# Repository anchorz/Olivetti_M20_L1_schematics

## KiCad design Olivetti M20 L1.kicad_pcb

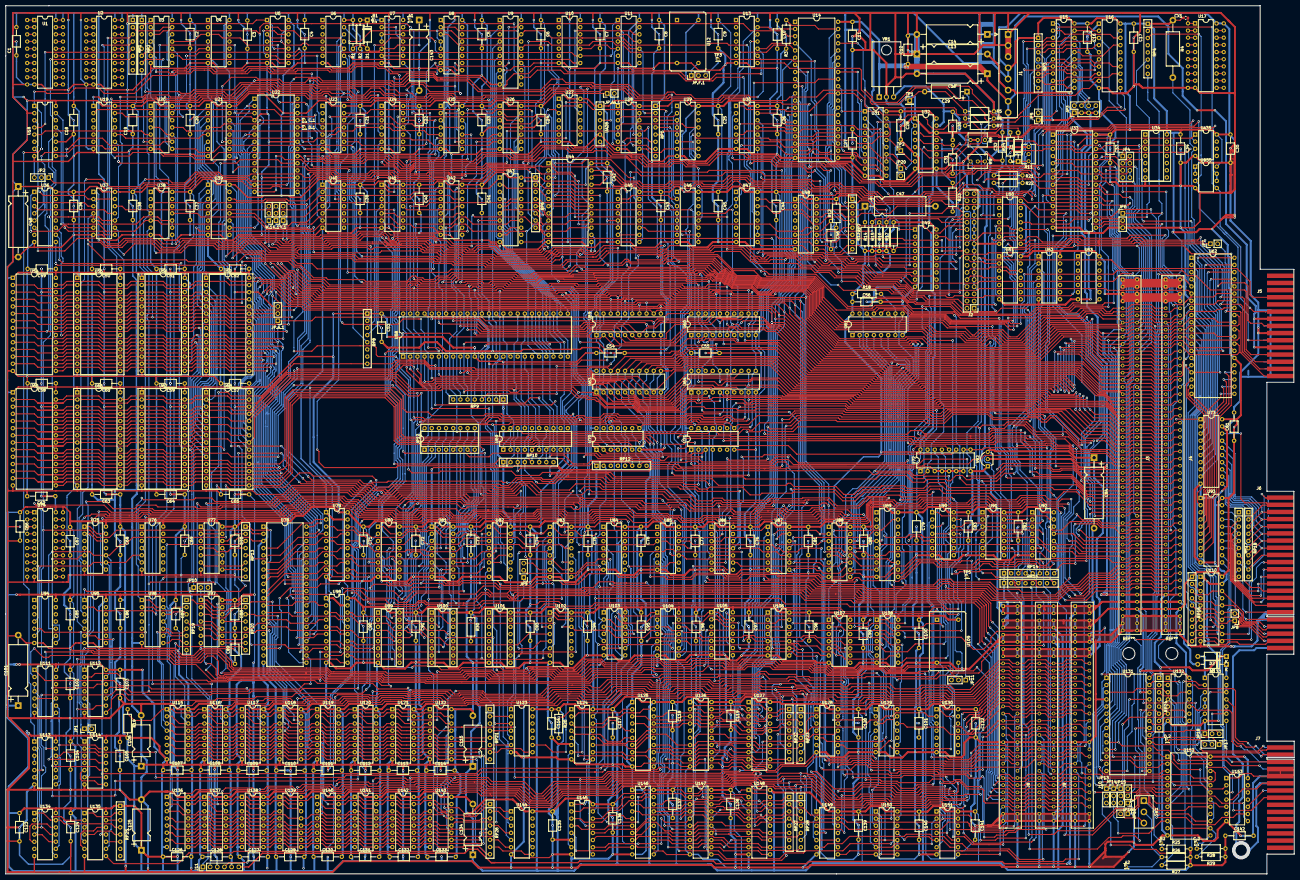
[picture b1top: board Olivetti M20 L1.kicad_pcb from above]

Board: 4 copper layers, 457.1 x 308.0 mm, 410 parts (0 on the bottom side), 747 nets.

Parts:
.A1, .A2, .B1, .B2: TestPoint; PinHeader_1x01_P1.00mm_Vertical
C1, C2, C3, C4, C5, C6, C7, C8, C9, C10, C11, C12, C16, C17, C18, C19, C20, C21, C22, C23, C24, C25, C26, C27, C28, C30, C33, C36, C37, C38, C39, C40, C41, C42, C43, C44, C45, C49, C50, C51, C52, C53, C54, C55, C56, C57, C58, C59, C60, C61, C62, C63, C64, C65, C66, C67, C68, C69, C70, C71, C72, C73, C74, C75, C76, C77, C78, C79, C80, C81, C82, C83, C85, C86, C87, C88, C89, C90, C91, C93, C94, C95, C96, C97, C98, C99, C100, C102, C103, C104, C105, C107, C108, C109, C110, C111, C112, C113, C114, C116, C117, C118, C119, C120, C121, C122, C123, C124, C126, C127, C128, C129, C130, C131, C132, C133, C135, C136, C137, C138, C139, C140, C141, C142: 100n; C_Axial_L3.8mm_D2.6mm_P10.00mm_Horizontal
C13, C14, C15, C48, C84: 47µ; CP_Axial_L18.0mm_D6.5mm_P25.00mm_Horizontal
C29: 0.68; CP_Axial_L10.0mm_D4.5mm_P15.00mm_Horizontal
C31: 100p; C_Axial_L3.8mm_D2.6mm_P10.00mm_Horizontal
C32, C46: C; C_Axial_L3.8mm_D2.6mm_P10.00mm_Horizontal
C34, C35: 1µ; C_Axial_L3.8mm_D2.6mm_P10.00mm_Horizontal
C47: 33µ; CP_Axial_L18.0mm_D6.5mm_P25.00mm_Horizontal
C101, C143: 22µ; CP_Axial_L18.0mm_D6.5mm_P25.00mm_Horizontal
C106, C115, C125, C134: 10µ; CP_Axial_L11.0mm_D6.0mm_P18.00mm_Horizontal
C.1, C.2: TestPoint; PinHeader_1x01_P1.00mm_Vertical
CX1: 1µ; C_0603_1608Metric
D1, D2, D3: 4148; D_A-405_P10.16mm_Horizontal
D.1, D.2: TestPoint; PinHeader_1x01_P1.00mm_Vertical
J1: 3.96mm; TE_826576-8_1x08_P3.96mm_Vertical
J2: Floppy Disk; PinHeader_2x17_P2.54mm_Vertical
J3, J4: EdgeCard100; Edge100
J5: VIDEO; Edge30_video
J6: Parallel; Edge44_pcb
J7: RS232; Edge30_pcb
J8, J9, J10: EdgeCard62; Edge62
J11: KBD; PinHeader_1x06_P2.54mm_Vertical
JP1: #DD; PinHeader_1x02_P2.54mm_Vertical
JP2: B; PinHeader_1x03_P2.54mm_Vertical
JP3: #X; PinHeader_2x04_P2.54mm_Vertical
JP4: Patch; PinHeader_2x04_P2.54mm_Vertical
JP5: #ZA; PinHeader_2x01_P2.54mm_Vertical
JP6: #E; PinHeader_1x03_P2.54mm_Vertical
JP7: #HH; PinHeader_1x02_P2.54mm_Vertical
JP8: #D; PinHeader_1x02_P2.54mm_Vertical
JP9: #JJ; PinHeader_1x03_P2.54mm_Vertical
JP10: #M; PinHeader_1x03_P2.54mm_Vertical
JP11: #G; PinHeader_1x03_P2.54mm_Vertical
JP12: Conn_02x08_Counter_Clockwise; DIP-16_W7.62mm_Socket
JP13: #C; PinHeader_1x03_P2.54mm_Vertical
JP14: #P; PinHeader_1x03_P2.54mm_Vertical
JP15: #N; PinHeader_1x03_P2.54mm_Vertical
JP16: #T; PinHeader_1x03_P2.54mm_Vertical
JP17: #R; PinHeader_1x03_P2.54mm_Vertical
JP18: #S; PinHeader_1x03_P2.54mm_Vertical
JP19: #FF; PinHeader_1x02_P2.54mm_Vertical
JP20: #CC; PinHeader_1x02_P2.54mm_Vertical
JP.A.1, JP.F.1: M20-Jumper.1; PinHeader_1x03_P2.54mm_Vertical
JP.AA.1: Conn_01x02_Male; PinHeader_1x02_P2.54mm_Vertical
K.1: M20-Jumper.2; PinHeader_1x03_P2.54mm_Vertical
R1: 22k; R_Axial_DIN0207_L6.3mm_D2.5mm_P10.16mm_Horizontal
R2: 47R; R_Axial_DIN0207_L6.3mm_D2.5mm_P10.16mm_Horizontal
R3: 10k; R_Axial_DIN0207_L6.3mm_D2.5mm_P10.16mm_Horizontal
R4: 30Ω; R_Axial_DIN0414_L11.9mm_D4.5mm_P20.32mm_Horizontal
R5, R6: 47.5k; R_Axial_DIN0207_L6.3mm_D2.5mm_P10.16mm_Horizontal
R7: 68; R_Axial_DIN0207_L6.3mm_D2.5mm_P10.16mm_Horizontal
R8: 100k; Potentiometer_Vishay_T73XW_Horizontal
R9: 50k; Potentiometer_Vishay_T73XW_Horizontal
R11: 10k; Potentiometer_Vishay_T73XW_Horizontal
R12, R14, R15, R16, R17, R21, R22: R; R_Axial_DIN0207_L6.3mm_D2.5mm_P10.16mm_Horizontal
R13: 47k; R_Axial_DIN0207_L6.3mm_D2.5mm_P10.16mm_Horizontal
R18, R20, R25, R26, R27, R28, R29: 1k; R_Axial_DIN0207_L6.3mm_D2.5mm_P10.16mm_Horizontal
R19, R24: 150R; R_Axial_DIN0207_L6.3mm_D2.5mm_P10.16mm_Horizontal
R23: 15k; R_Axial_DIN0207_L6.3mm_D2.5mm_P10.16mm_Horizontal
R30: 4.7k; R_Axial_DIN0207_L6.3mm_D2.5mm_P10.16mm_Horizontal
RP1, RP2, RP3, RP4, RP5, RP6, RP8, RP12, RP14, RP15, RP25: 1k; R_Array_SIP8
RP7, RP9, RP10: 10k; R_Array_SIP8
RP13, RP19, RP20: 33R; R_Array_SIP8
RP16, RP17, RP18: 1k; R_Array_SIP10
RP21, RP26: 33Ω; R_Array_SIP8
RP22, RP23, RP27, RP28: 120R; R_Array_SIP8
RP24: 27k; R_Array_SIP8
SW1: Reset-Button; TE_826576-3_1x03_P3.96mm_Vertical
TP1, TP2: TestPoint; PinHeader_1x01_P2.54mm_Vertical
TP3: TestPoint; PinHeader_1x01_P1.00mm_Vertical
TP5: EXT_PCLK; PinHeader_1x01_P1.00mm_Vertical
U1, U2, U17, U74: Spare20
U3, U25, U70, U87, U94, U149, U150: 'LS00; DIP-14_W7.62mm
U4, U30, U51: '16; DIP-14_W7.62mm
U5, U6, U52, U92: 'LS74; DIP-14_W7.62mm
U7: 'LS132; DIP-14_W7.62mm
U8, U42: 'LS138; DIP-16_W7.62mm
U9, U69, U79, U89, U98, U110, U127, U148: 'LS244; DIP-20_W7.62mm
U10, U13: 'LS32; DIP-14_W7.62mm
U11, U90, U134, U135: 'S74; DIP-14_W7.62mm
U12: 16MHz; Oscillator_DIP-14
U14: FD1797; DIP-40_W15.24mm
U15, U43, U125, U126, U146, U147: 'LS373; DIP-20_W7.62mm
U16: 'LS374; DIP-20_W7.62mm
U18: 'LS112; DIP-16_W7.62mm
U19, U77, U85, U91, U96, U108, U112, U123, U129, U144: 'S04; DIP-14_W7.62mm
U20, U50: 'S05; DIP-14_W7.62mm
U21, U39: 74LS138; DIP-16_W7.62mm
U22, U131: 8251; DIP-28_W15.24mm
U23, U103, U111, U130: 'S08; DIP-14_W7.62mm
U24, U95: 'LS02; DIP-14_W7.62mm
U26: 'LS260; DIP-14_W7.62mm
U27, U53: 'LS14; DIP-14_W7.62mm
U28, U97, U113, U114: 'S00; DIP-14_W7.62mm
U29, U45, U72: 74LS163; DIP-16_W7.62mm
U31: WD1691; DIP-20_W7.62mm
U32: 'LS629; DIP-16_W7.62mm
U33: 8259; DIP-28_W15.24mm
U34: SPARE; DIP-14_W7.62mm_Socket
U36: 'S138; DIP-16_W7.62mm
U37: 'LS08; DIP-14_W7.62mm
U38, U40, U86, U104: 'LS10; DIP-14_W7.62mm
U41: 'LS30; DIP-14_W7.62mm
U44: N82S181; DIP-24_W15.24mm
U46: 'LS163; DIP-16_W7.62mm
U47: 'LS123; DIP-16_W7.62mm
U48: 'LS221; DIP-16_W7.62mm
U49: WD2143M-03; DIP-18_W7.62mm
U54, U65: 27128; DIP-28_W15.24mm
U55, U56, U57, U66, U67, U68: 27128; DIP-28_W15.24mm_Socket
U58: Z8001; DIP-48_W15.24mm
U59, U63: 'S245; DIP-20_W7.62mm
U60, U64: 'S373; DIP-20_W7.62mm
U61: 'S163; DIP-16_W7.62mm
U62: 8255; DIP-40_W15.24mm
U71, U128: 'LS04; DIP-14_W7.62mm
U73, U93: 'LS245; DIP-20_W7.62mm
U75, U105, U107: 'LS20; DIP-14_W7.62mm
U76, U106: 'S32; DIP-14_W7.62mm
U78: MC6845; DIP-40_W15.24mm
U80, U81, U82, U83, U102: 'S253; DIP-16_W7.62mm
U84: PE-21389; DIP-14_W7.62mm
U88: 'LS670; DIP-16_W7.62mm
U99, U100, U101: SPARE; DIP-16_W7.62mm_Socket
U109: 12MHz; Oscillator_DIP-14
U115, U116, U117, U118, U119, U120, U121, U122, U136, U137, U138, U139, U140, U141, U142, U143: 41256; DIP-16_W7.62mm
U124, U145: 'LS166; DIP-16_W7.62mm
U132, U153: 75189; DIP-14_W7.62mm
U133: 75188; DIP-14_W7.62mm
U151: 'S20; DIP-14_W7.62mm
U152: 8253; DIP-24_W15.24mm
UA28: HH3006A; R_Array_SIP6
UA35: 75451; DIP-8_W7.62mm
UB35: 75451; DIP-8_W7.62mm
V.1: M20-Jumper.1; PinHeader_1x03_P2.54mm_Vertical
VR1: UA7805UC; TO-220-3_Horizontal_TabDown
VR2: 79L05; TO-92_Inline_Wide
W.1: M20-Jumper.2; PinHeader_1x03_P2.54mm_Vertical
Z1: 8.2V; D_A-405_P10.16mm_Horizontal

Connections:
32^128: JP3.6, RP3.3, U15.17, U44.1
+5P: C1.1, C2.1, C3.1, C4.1, C5.1, C6.1, C7.1, C8.1, C9.1, C10.1, C13.1, C16.1, C17.1, C18.1, C19.1, C20.1, C21.1, C22.1, C23.1, C24.1, C25.1, C26.1, C27.1, C28.1, C33.1, C34.1, C35.1, C36.1, C37.1, C38.1, C39.1, C40.1, C41.1, C42.1, C43.1, C44.1, C45.1, C48.1, C49.1, C50.1, C51.1, C52.1, C53.1, C54.1, C55.1, C56.1, C57.1, C58.1, C59.1, C60.1, C61.1, C62.1, C63.1, C64.1, C65.1, C66.1, C67.1, C68.1, C69.1, C70.1, C71.1, C72.1, C73.1, C74.1, C75.1, C76.1, C77.1, C78.1, C79.1, C80.1, C81.1, C82.1, C83.1, C85.1, C86.1, C87.1, C88.1, C89.1, C90.1, C91.1, C93.1, C94.1, C95.1, C96.1, C97.1, C98.1, C99.1, C100.1, C101.1, C102.1, C103.1, C104.1, C105.1, C106.1, C107.1, C108.1, C109.1, C110.1, C111.1, C112.1, C113.1, C114.1, C115.1, C116.1, C117.1, C118.1, C119.1, C120.1, C121.1, C122.1, C123.1, C124.1, C125.1, C126.1, C127.1, C128.1, C129.1, C130.1, C131.1, C132.1, C133.1, C134.1, C135.1, C136.1, C137.1, C138.1, C139.1, C140.1, C141.1, C142.1, CX1.1, J1.4, J1.5, J3.5, J3.6, J3.7, J3.8, J3.93, J3.94, J4.5, J4.6, J4.7, J4.8, J4.93, J4.94, J8.5, J8.6, J8.7, J8.8, J9.5, J9.6, J9.7, J9.8, J10.5, J10.6, J10.7, J10.8, J11.3, JP.A.1.3, R1.1, R2.2, R3.2, R4.1, R12.2, R13.1, R14.1, R15.1, R16.1, R17.2, R18.1, R19.2, R20.1, R25.2, R26.2, R27.1, R28.1, R29.1, R30.1, RP1.1, RP2.1, RP3.1, RP4.1, RP5.1, RP6.1, RP7.1, RP8.1, RP9.1, RP10.1, RP12.1, RP14.1, RP15.1, RP16.1, RP17.1, RP18.1, RP25.1, U1.20, U1.40, U2.20, U2.40, U3.14, U4.14, U5.14, U6.14, U7.14, U8.16, U9.20, U10.14, U11.14, U12.14, U13.14, U14.21, U15.20, U16.20, U17.20, U17.40, U18.16, U19.14, U20.14, U21.16, U22.26, U23.14, U24.14, U25.14, U26.14, U27.14, U28.14, U29.16, U30.14, U31.20, U32.16, U33.28, U34.14, U36.16, U37.14, U38.14, U39.16, U40.14, U41.14, U42.16, U43.20, U44.24, U45.16, U46.16, U47.16, U48.16, U49.18, U50.14, U51.14, U52.14, U53.14, U54.1, U54.26, U54.28, U55.1, U55.26, U55.28, U56.1, U56.26, U56.28, U57.1, U57.26, U57.28, U58.11, U59.20, U60.20, U61.16, U62.26, U63.20, U64.20, U65.1, U65.26, U65.28, U66.1, U66.26, U66.28, U67.1, U67.26, U67.28, U68.1, U68.26, U68.28, U69.20, U70.14, U71.14, U72.16, U73.20, U74.20, U74.40, U75.14, U76.14, U77.14, U78.20, U79.20, U80.16, U81.16, U82.16, U83.16, U84.14, U85.14, U86.14, U87.14, U88.16, U89.20, U90.14, U91.14, U92.14, U93.20, U94.14, U95.14, U96.14, U97.14, U98.20, U99.16, U100.16, U101.16, U102.16, U103.14, U104.14, U105.14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
+5VA: C30.1, C32.1, R8.2, R8.3, R21.1, U32.15, VR1.3
+12V: C11.1, C12.1, C15.1, D3.2, J1.7, J1.8, J3.91, J3.92, J4.91, J4.92, J5.14, J5.22, J8.1, J8.2, J8.3, J8.4, J9.1, J9.2, J9.3, J9.4, J10.1, J10.2, J10.3, J10.4, J11.6, R24.2, U14.40, VR1.1
-5V: C84.1, J8.13, J8.14, J8.15, J8.16, J9.13, J9.14, J9.15, J9.16, J10.13, J10.14, J10.15, J10.16, VR2.3
-12V: C14.2, D2.1, J1.6, J3.89, J3.90, J4.89, J4.90, RP24.1, VR2.2
-PCLK: U52.3, U85.4, U92.12, U107.1
/AD Mux/PL024: U59.19, U63.19, U70.6
/CLK_IO/PM002: U11.8, U28.10
/CLK_IO/PM003: U28.8, U29.7, U29.10
/CLK_IO/PM004: JP.F.1.1, U12.8
/CLK_IO/PM005: U11.3, U11.11, U28.3, U29.2, U45.2, U46.2
/CLK_IO/PM006: JP.F.1.2, U28.1, U28.2
/CLK_IO/PM010: U28.11, U45.9
/CLK_IO/PM011: U28.12, U28.13, U45.15
/CLK_IO/PM012: U11.12, U27.12
/CLK_IO/PM013: U27.2, U27.13
/CLK_IO/PM016: U3.2, U3.4, U24.13
/CLK_IO/PM017: U19.11, U26.5, U39.6
/CLK_IO/PM018: U19.10, U21.5
/CLK_IO/PM019: JP.F.1.3, TP3.1
/CLK_IO/PZ128: JP.AA.1.2, U28.6
/CLK_IO/R1402: RP5.3, U29.1, U29.3, U29.4, U29.5, U29.6, U29.9
/CLK_IO/RP5A: RP5.2, U11.4, U11.10
/CLK_IO/RP5F: RP5.7, U11.13
/CPU/PK000: U7.3, U7.4, U7.12
/CPU/PK001: U7.2, U7.11
/CPU/PK002: U7.6, U7.9, U7.10, U50.9
/CPU/PK003: U7.8, U58.16
/CPU/PK004: U6.9, U58.14
/CPU/PK005: U6.12, U40.12
/CPU/PK006: U25.3, U40.1
/CPU/PK011: U43.3, U58.26
/CPU/PK012: U43.4, U58.25
/CPU/PK013: U43.7, U58.37
/CPU/PK014: U43.8, U58.24
/CPU/PK015: U43.13, U58.42
/CPU/PK016: U43.14, U58.46
/CPU/PK017: U43.17, U58.47
/CPU/PK022: U8.7, U20.13
/CPU/PK030: U19.13, U26.6
/CPU/PK031: U19.12, U40.2
/CPU/PK033: U33.19, U91.8
/CPU/PK034: U33.20, U91.10
/CPU/PK037: U33.25, U91.6
/CPU/PK038: U33.17, U50.11
/CPU/PK040: U5.6, U5.12, U23.4
/CPU/PK041: U3.9, U5.8
/CPU/PK042: U3.8, U3.12
/CPU/PZ116: U8.9, U23.9
/CPU/R0028: C143.1, D1.2, R1.2, U7.5
/CPU/R0033: .B1.1, .B2.1, R25.1, SW1.1, U7.1
/CPU/R0034: .A1.1, .A2.1, R26.1, SW1.2, U7.13
/CPU/R0035: D1.1, R2.1
/CPU/R0705: RP9.8, U58.7
/CPU/R0706: RP9.7, U58.8
/CPU/XA.4.4: RP2.6, U4.4, U4.5
/CPU/XR.2.2: RP2.2, U5.1, U5.10
/CRTC/PE000: U78.4, U79.2
/CRTC/PE001: U78.5, U79.4
/CRTC/PE002: U78.6, U79.17
/CRTC/PE003: U78.7, U79.6
/CRTC/PE004: U78.8, U79.15
/CRTC/PE005: U78.9, U79.8
/CRTC/PE006: U78.10, U79.13
/CRTC/PE007: U78.11, U79.11
/CRTC/PE008: U78.12, U98.2
/CRTC/PE009: U78.13, U98.17
/CRTC/PE010: U78.14, U98.4
/CRTC/PE011: U78.15, U98.15
/CRTC/PE012: U78.38, U98.6
/CRTC/PE013: U78.37, U98.13
/CRTC/PE014: U78.36, U98.8
/CRTC/PE015: U78.35, U98.11
/CRTC/PZ054: R30.2, U102.15
/DRAM/PD000: JP10.2, U97.1, U97.4, U97.10, U97.13
/DRAM/PD003.1: RP13.5, U119.3, U120.3, U121.3, U122.3
/DRAM/PD003.2: RP13.8, U115.3, U116.3, U117.3, U118.3
/DRAM/PD004.1: RP19.3, U96.12
/DRAM/PD004.2: RP19.5, U96.10
/DRAM/PD005.1: RP19.4, U119.4, U120.4, U121.4, U122.4
/DRAM/PD005.2: RP19.6, U115.4, U116.4, U117.4, U118.4
/DRAM/PD007.1: RP20.5, U119.15, U120.15, U121.15, U122.15
/DRAM/PD007.2: RP20.8, U115.15, U116.15, U117.15, U118.15
/DRAM/PD009: RP21.1, U115.5, U116.5, U117.5, U118.5, U119.5, U120.5, U121.5, U122.5, U136.5, U137.5, U138.5, U139.5, U140.5, U141.5, U142.5, U143.5
/DRAM/PD011: RP21.8, U115.7, U116.7, U117.7, U118.7, U119.7, U120.7, U121.7, U122.7, U136.7, U137.7, U138.7, U139.7, U140.7, U141.7, U142.7, U143.7
/DRAM/PD013: RP21.3, U115.6, U116.6, U117.6, U118.6, U119.6, U120.6, U121.6, U122.6, U136.6, U137.6, U138.6, U139.6, U140.6, U141.6, U142.6, U143.6
/DRAM/PD015: RP21.5, U115.12, U116.12, U117.12, U118.12, U119.12, U120.12, U121.12, U122.12, U136.12, U137.12, U138.12, U139.12, U140.12, U141.12, U142.12, U143.12
/DRAM/PD016: RP26.2, U144.2
/DRAM/PD017: RP26.1, U115.11, U116.11, U117.11, U118.11, U119.11, U120.11, U121.11, U122.11, U136.11, U137.11, U138.11, U139.11, U140.11, U141.11, U142.11, U143.11
/DRAM/PD018: RP26.6, U144.6
/DRAM/PD019: RP26.5, U115.10, U116.10, U117.10, U118.10, U119.10, U120.10, U121.10, U122.10, U136.10, U137.10, U138.10, U139.10, U140.10, U141.10, U142.10, U143.10
/DRAM/PD020: RP26.4, U144.4
/DRAM/PD021: RP26.3, U115.13, U116.13, U117.13, U118.13, U119.13, U120.13, U121.13, U122.13, U136.13, U137.13, U138.13, U139.13, U140.13, U141.13, U142.13, U143.13
/DRAM/PD024: RP26.8, U115.9, U116.9, U117.9, U118.9, U119.9, U120.9, U121.9, U122.9, U136.9, U137.9, U138.9, U139.9, U140.9, U141.9, U142.9, U143.9
/DRAM/PD025: RP20.4, U97.11
/DRAM/PD026.1: RP20.3, U140.15, U141.15, U142.15, U143.15
/DRAM/PD026.2: RP20.1, U136.15, U137.15, U138.15, U139.15
/DRAM/PD027.1: RP19.2, U96.2
/DRAM/PD027.2: RP19.7, U96.8
/DRAM/PD028.1: RP19.1, U140.4, U141.4, U142.4, U143.4
/DRAM/PD028.2: RP19.8, U136.4, U137.4, U138.4, U139.4
/DRAM/PD029: U77.2, U77.3, U77.13
/DRAM/PD030.1: RP13.2, U77.12
/DRAM/PD030.2: RP13.4, U77.4
/DRAM/PD031.1: RP13.1, U140.3, U141.3, U142.3, U143.3
/DRAM/PD031.2: RP13.3, U136.3, U137.3, U138.3, U139.3
/DRAM/PD032: R19.1, U115.1, U116.1, U117.1, U118.1, U119.1, U120.1, U121.1, U122.1, U136.1, U137.1, U138.1, U139.1, U140.1, U141.1, U142.1, U143.1
/DRAM/ras.int: U96.1, U96.9, U96.11, U96.13, U129.2
/FDC+Latch/PA000: U15.3, U16.2, U51.3
/FDC+Latch/PA001: U15.4, U16.5, U51.13
/FDC+Latch/PA002: U15.7, U16.6, U51.1
/FDC+Latch/PA003: U14.37, U16.9, U31.15
/FDC+Latch/PA004: JP5.2, RP3.8, U15.8
/FDC+Latch/PA005: U14.26, U31.12
/FDC+Latch/PA006: U14.30, U30.1, U31.7
/FDC+Latch/PA007: JP20.2, U14.31, U31.1
/FDC+Latch/PA008: U14.17, U31.17
/FDC+Latch/PA009: U14.18, U31.18
/FDC+Latch/PA010: U14.33, U31.8
/FDC+Latch/PA011: JP20.1, U30.9, U31.6
/FDC+Latch/PA012: C29.2, R5.1, R6.1, TP1.1, U31.13, U31.14, U32.2
/FDC+Latch/PA015: R9.3, R22.1, R23.1, U32.3
/FDC+Latch/PA016: C31.2, U32.4
/FDC+Latch/PA017: C31.1, U32.5
/FDC+Latch/PA018: U14.27, U31.11, U48.12
/FDC+Latch/PA019: U13.8, U15.1
/FDC+Latch/PA022: U13.11, U16.11
/FDC+Latch/PA023: U14.23, U14.28
/FDC+Latch/PA024: U14.32, U47.13
/FDC+Latch/PA025: U14.25, U30.5
/FDC+Latch/PA026: U14.16, U30.11
/FDC+Latch/PA027: U14.15, U30.13
/FDC+Latch/PA031: RP7.7, U47.2, U47.3
/FDC+Latch/PA032: C47.2, U47.14
/FDC+Latch/PA046: TP2.1, U31.16, U32.7
/FDC+Latch/PA080: U31.19, U49.1
/FDC+Latch/PA081: U31.3, U49.3
/FDC+Latch/PA082: U31.2, U49.5
/FDC+Latch/PA083: U31.4, U49.7
/FDC+Latch/PA084: U16.19, U31.9
/FDC+Latch/PA085: R11.2, U49.17
/FDC+Latch/PA086: U31.5, U49.11
/FDC+Latch/PA087: R11.1, R24.1, Z1.1
/Latch/PC003: U124.2, U125.2
/Latch/PC004: U124.3, U125.5
/Latch/PC005: U124.4, U125.6
/Latch/PC006: U124.5, U125.9
/Latch/PC007: U124.10, U125.12
/Latch/PC008: U124.11, U125.15
/Latch/PC009: U124.12, U125.16
/Latch/PC010: U124.14, U125.19
/Latch/PC011: U145.2, U146.2
/Latch/PC012: U145.3, U146.5
/Latch/PC013: U145.4, U146.6
/Latch/PC014: U145.5, U146.9
/Latch/PC015: U145.10, U146.12
/Latch/PC016: U145.11, U146.15
/Latch/PC017: U145.12, U146.16
/Latch/PC018: U145.14, U146.19
/Latch/PC019: U105.6, U127.1, U127.19
/Latch/PC020: U124.13, U145.1
/Latch/PC023: U105.8, U148.1, U148.19
/Latch/PC024: RP23.2, U125.3, U126.3, U127.18
/Latch/PC025: RP23.4, U125.4, U126.4, U127.16
/Latch/PC026: RP22.6, U125.7, U126.7, U127.14
/Latch/PC027: RP22.8, U125.8, U126.8, U127.12
/Latch/PC028: RP23.8, U125.13, U126.13, U127.9
/Latch/PC029: RP23.6, U125.14, U126.14, U127.7
/Latch/PC030: RP22.3, U125.17, U126.17, U127.5
/Latch/PC031: RP22.1, U125.18, U126.18, U127.3
/Latch/PC032: RP28.2, U146.3, U147.3, U148.18
/Latch/PC033: RP28.4, U146.4, U147.4, U148.16
/Latch/PC034: RP27.6, U146.7, U147.7, U148.14
/Latch/PC035: RP27.8, U146.8, U147.8, U148.12
/Latch/PC036: RP28.8, U146.13, U147.13, U148.9
/Latch/PC037: RP28.6, U146.14, U147.14, U148.7
/Latch/PC038: RP27.3, U146.17, U147.17, U148.5
/Latch/PC039: RP27.1, U146.18, U147.18, U148.3
/Latch/SRAM: U86.3, U87.3
/PIO/PJ000: U62.4, U73.2
/PIO/PJ001: U62.3, U73.3
/PIO/PJ002: U62.2, U73.4
/PIO/PJ003: U62.1, U73.5
/PIO/PJ004: U62.40, U73.6
/PIO/PJ005: U62.39, U73.7
/PIO/PJ006: U62.38, U73.8
/PIO/PJ007: U62.37, U73.9
/PIO/PJ008: U62.18, U93.2
/PIO/PJ009: U62.19, U93.3
/PIO/PJ010: U62.20, U93.4
/PIO/PJ011: U62.21, U93.5
/PIO/PJ012: U62.22, U93.6
/PIO/PJ013: U62.23, U93.7
/PIO/PJ014: U62.24, U93.8
/PIO/PJ015: U62.25, U93.9
/PIO/PJ016: U62.15, U110.4
/PIO/PJ017: U62.16, U110.5
/PIO/PJ018: U62.13, U110.13
/PIO/PJ019: U62.12, U110.8
/PIO/PJ020: U62.11, U110.9
/PIO/PJ021: U62.10, U110.17
/PIO/PJ022: U92.3, U152.17
/PIO/R0302: RP16.6, U73.1
/PIO/R4907: RP14.5, U92.2, U92.4
/ROM/PG000: U38.6, U54.22, U55.22, U56.22, U57.22, U65.22, U66.22, U67.22, U68.22
/ROM/PG001: JP.A.1.2, U54.23, U55.23, U56.23, U57.23, U65.23, U66.23, U67.23, U68.23
/ROM/PG006: U36.15, U54.20, U65.20
/ROM/PG007: U36.11, U55.20, U66.20
/ROM/PG008: U36.10, U56.20, U67.20
/ROM/PG009: U36.9, U57.20, U68.20
/ROM/PG010: U36.1, U37.6
/ROM/PG011: U36.2, U37.3
/ROM/PG012: U36.3, U37.11
/ROM/PG013: U18.3, U18.7, U37.2, U37.5, U37.13, U38.9, U38.10
/ROM/PG014: U36.6, U38.8
/ROM/PG016: U18.5, U20.5
/ROM/PG017: U18.15, U37.8
/ROM/PG018: U19.8, U36.5
/ROM/R0007: RP1.4, U54.27, U55.27, U56.27, U57.27
/ROM/R2007: RP1.3, U65.27, U66.27, U67.27, U68.27
/ROM/R2907: RP1.5, U18.4
/ROM/R3907: RP1.6, U18.14
/ROM/XA.23.11: U20.11, U23.11
/ROM/XA.25.8: U23.13, U25.8
/ROM/XA.27.4: U20.3, U27.4
/Serial/PH004: U131.3, U132.3
/Serial/PH005: JP15.1, U132.6
/Serial/PH006: JP16.3, U132.8
/Serial/PH007: JP16.2, U131.17
/Serial/PH008: U131.22, U132.11
/Serial/PH009: U131.19, U133.4, U133.5
/Serial/PH010: JP18.3, U131.23
/Serial/PH011: JP17.1, U131.24
/Serial/PH012: JP18.2, U133.9, U133.10
/Serial/PH013: JP17.2, U133.12, U133.13
/Serial/PH020: JP15.3, U131.25
/Serial/PH022: JP13.2, U133.2
/Serial/PH038: RP24.8, U153.9
/Serial/PH039: RP24.6, U153.5
/Serial/PH040: RP24.7, U153.2
/State/PF011: U61.1, U90.9, U130.1
/State/PF012: U53.8, U87.12, U88.11
/State/PF013: U87.11, U89.19
/State/PF015: U52.5, U90.12
/State/PF016: U90.3, U108.8
/State/PF017: U90.5, UA35.1
/State/PF018: U72.14, U108.13
/State/PF019: U72.13, U107.4
/State/PF020: U72.12, U108.1
/State/PF021: U107.5, U108.2
/State/PF022: JP11.3, U109.8
/State/PF029: JP11.2, U87.9, U87.10, U108.3, U108.11
/State/PF031: JP6.2, U53.9
/State/PF081: U61.9, U90.8
/State/R1402: RP14.7, U72.1, U72.3, U72.4, U72.5, U72.6, U72.7, U72.9, U72.10
/State/RP14E: RP14.6, U52.4, U90.4, U90.10
/State/color_write: U88.12, U106.11
/Timings/A0=0: U150.1, U150.8
/Timings/Delay+50: U84.12, U103.10
/Timings/Delay+100: U84.4, U103.4
/Timings/Delay+150: U84.10, U103.13
/Timings/Delay+200: U84.6, U103.1
/Timings/Delay+250: U84.8, U114.2
/Timings/PB000: U41.1, U42.15
/Timings/PB001: U41.12, U42.14
/Timings/PB002: U41.11, U42.13
/Timings/PB003: U41.5, U42.12
/Timings/PB004: U42.11, U149.1
/Timings/PB005: U42.10, U128.9, U149.12
/Timings/PB006: U42.9, U128.5, U149.4
/Timings/PB007: U42.7, U128.11, U149.9
/Timings/PB008: U42.4, U95.6, U104.13, U135.9
/Timings/PB010: U25.4, U25.11, U40.5
/Timings/PB011: U24.4, U25.5, U40.4
/Timings/PB022: U75.2, U75.12, U95.4
/Timings/PB023: U75.4, U75.5, U94.8
/Timings/PB024: U75.10, U94.10, U112.10, U151.4, U151.10
/Timings/PB035: U129.8, U150.13
/Timings/PB036: U85.8, U85.11, U85.13, U112.1
/Timings/PB039: U150.11, U151.5, U151.9
/Timings/PB040: U94.9, U112.12
/Timings/PZ023: U86.9, U128.4
/Timings/R1102: RP8.4, U41.2, U41.3, U41.4
/Timings/R1102.A: RP25.2, U135.1
/Timings/R1102.B: RP25.3, U135.13
/Timings/R1102.C: RP25.4, U134.1, U134.13
/Timings/R1102.D: RP25.5, U135.4
/Timings/R1102.E: RP25.6, U135.10
/Timings/R1105: RP8.2, W.1.1
/Timings/X.103.3: U103.3, U104.2, U104.3, U104.9, U129.9
/Timings/X.103.6: U75.1, U75.13, U85.5, U103.6, U104.1, U104.4
/Timings/X.104.6: U104.6, U111.2, U128.1
/Timings/X.134.9: U111.9, U114.13, U134.9
/Timings/X.RP12A: RP12.2, U103.2, U103.5, U103.9, U103.12
/Timings/XA.25.6: U25.6, U95.3
/Timings/XA.76.6: U42.6, U76.6
/Timings/XA.104.12: U104.12, U113.13, U128.13
/Timings/XA.111.8: U111.8, U114.10
AAA00: J3.30, J4.30, U60.2, U150.5, U150.9, U150.10
AAA01: J3.29, J4.29, U14.5, U22.12, U33.27, U54.10, U55.10, U56.10, U57.10, U60.5, U62.9, U65.10, U66.10, U67.10, U68.10, U78.24, U83.5, U88.14, U102.5, U131.12, U152.19
AAA02: J3.32, J4.32, U14.6, U54.9, U55.9, U56.9, U57.9, U60.6, U62.8, U65.9, U66.9, U67.9, U68.9, U83.11, U88.13, U152.20
AAA03: J3.31, J4.31, U18.12, U54.8, U55.8, U56.8, U57.8, U60.9, U65.8, U66.8, U67.8, U68.8, U82.5
AAA04: J3.34, J4.34, U54.7, U55.7, U56.7, U57.7, U60.12, U65.7, U66.7, U67.7, U68.7, U82.11
AAA05: J3.33, J4.33, U21.1, U39.1, U54.6, U55.6, U56.6, U57.6, U60.15, U65.6, U66.6, U67.6, U68.6, U81.5
AAA06: J3.36, J4.36, U21.2, U39.2, U54.5, U55.5, U56.5, U57.5, U60.16, U65.5, U66.5, U67.5, U68.5, U81.11
AAA07: J3.35, J4.35, U21.3, U39.3, U54.4, U55.4, U56.4, U57.4, U60.19, U65.4, U66.4, U67.4, U68.4, U80.5
AAA08: J3.38, J4.38, U21.6, U39.5, U54.3, U55.3, U56.3, U57.3, U64.2, U65.3, U66.3, U67.3, U68.3, U80.11, U83.6
AAA09: J3.37, J4.37, U54.25, U55.25, U56.25, U57.25, U64.5, U65.25, U66.25, U67.25, U68.25, U83.10
AAA10: J3.40, J4.40, U54.24, U55.24, U56.24, U57.24, U64.6, U65.24, U66.24, U67.24, U68.24, U82.6
AAA11: J3.39, J4.39, U26.13, U54.21, U55.21, U56.21, U57.21, U64.9, U65.21, U66.21, U67.21, U68.21, U82.10
AAA12: J3.42, J4.42, JP.A.1.1, U26.12, U64.12, U81.6
AAA13: J3.41, J4.41, U26.1, U54.2, U55.2, U56.2, U57.2, U64.15, U65.2, U66.2, U67.2, U68.2, U81.10
AAA14: J3.44, J4.44, U26.2, U44.8, U64.16
AAA15: J3.43, J4.43, U26.3, U44.7, U64.19
ADX0: JP9.1, U102.7, U123.1
AS: U43.11, U60.11, U64.11, U71.10
BANK0: U42.1, V.1.2
BANK1: K.1.2, U42.2
BANKH: U42.3, W.1.2
BL.SerClk: C.1.1, C.2.1, R28.2, U22.9, U22.25, U152.13
BLUE: J5.24, U61.12
BOOT: U18.9, U20.9, U24.5
BRIGHT: J5.30, JP7.2
BUSRQ: J3.65, J4.65, RP9.6, U58.27
BWCS1: J8.46, U128.8
BWCS2: J9.46, U128.6
BWCS3: J10.46, U128.10
BW^COL: J8.36, J9.36, J10.36, JP3.4, RP3.2, U15.18, U44.23
BW_VIDEO: J5.16, R4.2, UA35.3
Bl.DTR: D.1.1, D.2.1, JP17.3, U22.24
Byte+0: U105.4, U150.3, U151.12
Byte+1: U105.9, U150.6, U151.2
B~W: J3.82, J4.82, RP10.3, U69.3, U150.2, U150.4
CAS0: J3.74, J4.74, U33.12
CAS1: J3.73, J4.73, U33.13
CAS2: J3.71, J4.71, U33.15
CAS.H: J8.43, J9.43, J10.43, U85.10, U97.2, U97.12
CAS.L: J8.44, J9.44, J10.44, U85.12, U97.5, U97.9
CASC: J8.41, J9.41, J10.41, U112.2
CLK.1MHz: U14.24, U46.11
CLK.2: U19.2, U23.5
CLK.2MHz: U22.20, U46.12, U131.20
CLK.4MHz: J3.76, J4.76, U46.13
CLK_TIMER: U45.11, U152.9, U152.15, U152.18
COL4^8: JP3.8, RP3.5, U15.14, U44.22
COLOR_CS1: J8.47, U149.11
COLOR_CS2: J9.47, U149.6
COLOR_CS3: J10.47, U149.8
COMVI1: J3.69, J4.69, RP15.3, U91.9
COMVI2: J3.72, J4.72, RP14.3, U91.11
CPU.B~W: U58.32, U69.17
CPU.CLK: U58.35, UA28.6
CPU.N~S: U58.31, U69.4
CPU.RW: U58.30, U69.8, U69.13
CPU.ST0: U9.8, U58.23
CPU.ST1: U9.6, U58.22
CPU.ST2: U9.4, U58.21
CPU.ST3: U9.2, U58.20
CPU.~AS: U58.34, U69.2
CPU.~BUSACK: RP12.6, U58.29, U70.10
CPU.~DS: U58.19, U69.15
CPU.~MREQ: U58.18, U69.6
CPU.~WAIT: RP9.5, U20.4, U20.10, U58.28
CPU_OR_CRT: J3.86, J4.86, U86.13, U105.5, U105.10, U112.9, U135.5
D0: J8.18, J9.18, J10.18, RP23.1, U122.2, U122.14
D1: J8.17, J9.17, J10.17, RP23.3, U121.2, U121.14
D2: J8.20, J9.20, J10.20, RP22.5, U120.2, U120.14
D3: J8.19, J9.19, J10.19, RP22.7, U119.2, U119.14
D4: J8.22, J9.22, J10.22, RP23.7, U118.2, U118.14
D5: J8.21, J9.21, J10.21, RP23.5, U117.2, U117.14
D6: J8.24, J9.24, J10.24, RP22.4, U116.2, U116.14
D7: J8.23, J9.23, J10.23, RP22.2, U115.2, U115.14
D8: J8.25, J9.25, J10.25, RP28.1, U136.2, U136.14
D9: J8.26, J9.26, J10.26, RP28.3, U137.2, U137.14
D10: J8.27, J9.27, J10.27, RP27.5, U138.2, U138.14
D11: J8.28, J9.28, J10.28, RP27.7, U139.2, U139.14
D12: J8.29, J9.29, J10.29, RP28.7, U140.2, U140.14
D13: J8.30, J9.30, J10.30, RP28.5, U141.2, U141.14
D14: J8.31, J9.31, J10.31, RP27.4, U142.2, U142.14
D15: J8.32, J9.32, J10.32, RP27.2, U143.2, U143.14
DDD00: J3.14, J4.14, U4.6, U14.7, U15.2, U16.3, U22.27, U54.11, U55.11, U56.11, U57.11, U59.18, U62.34, U78.33, U88.15, U126.2, U127.2, U131.27, U152.8
DDD01: J3.13, J4.13, U14.8, U15.5, U16.4, U22.28, U33.11, U54.12, U55.12, U56.12, U57.12, U59.17, U62.33, U78.32, U88.1, U126.5, U127.4, U131.28, U152.7
DDD02: J3.16, J4.16, U14.9, U15.6, U16.7, U22.1, U33.10, U54.13, U55.13, U56.13, U57.13, U59.16, U62.32, U78.31, U88.2, U126.6, U127.6, U131.1, U152.6
DDD03: J3.15, J4.15, U14.10, U15.9, U16.8, U22.2, U33.9, U54.15, U55.15, U56.15, U57.15, U59.15, U62.31, U78.30, U88.3, U126.9, U127.8, U131.2, U152.5
DDD04: J3.18, J4.18, U14.11, U15.12, U16.13, U22.5, U33.8, U54.16, U55.16, U56.16, U57.16, U59.14, U62.30, U78.29, U126.12, U127.11, U131.5, U152.4
DDD05: J3.17, J4.17, U14.12, U15.15, U16.14, U22.6, U33.7, U54.17, U55.17, U56.17, U57.17, U59.13, U62.29, U78.28, U126.15, U127.13, U131.6, U152.3
DDD06: J3.20, J4.20, U14.13, U15.16, U16.17, U22.7, U33.6, U54.18, U55.18, U56.18, U57.18, U59.12, U62.28, U78.27, U126.16, U127.15, U131.7, U152.2
DDD07: J3.19, J4.19, U14.14, U15.19, U16.18, U22.8, U33.5, U54.19, U55.19, U56.19, U57.19, U59.11, U62.27, U78.26, U126.19, U127.17, U131.8, U152.1
DDD08: J3.22, J4.22, U33.4, U63.18, U65.11, U66.11, U67.11, U68.11, U147.2, U148.2
DDD09: J3.21, J4.21, U63.17, U65.12, U66.12, U67.12, U68.12, U147.5, U148.4
DDD10: J3.24, J4.24, U63.16, U65.13, U66.13, U67.13, U68.13, U147.6, U148.6
DDD11: J3.23, J4.23, U63.15, U65.15, U66.15, U67.15, U68.15, U147.9, U148.8
DDD12: J3.26, J4.26, U63.14, U65.16, U66.16, U67.16, U68.16, U147.12, U148.11
DDD13: J3.25, J4.25, U63.13, U65.17, U66.17, U67.17, U68.17, U147.15, U148.13
DDD14: J3.28, J4.28, U63.12, U65.18, U66.18, U67.18, U68.18, U147.16, U148.15
DDD15: J3.27, J4.27, U63.11, U65.19, U66.19, U67.19, U68.19, U147.19, U148.17
DS: U18.13, U38.5, U71.2, U78.23
DX0: J8.49, J9.49, J10.49, JP9.2
Direction: J2.18, U30.10
DispEn: U52.2, U78.18
EXT_PCLK: J5.8, JP11.1, TP5.1
GND: C1.2, C2.2, C3.2, C4.2, C5.2, C6.2, C7.2, C8.2, C9.2, C10.2, C11.2, C12.2, C13.2, C14.1, C15.2, C16.2, C17.2, C18.2, C19.2, C20.2, C21.2, C22.2, C23.2, C24.2, C25.2, C26.2, C27.2, C28.2, C30.2, C32.2, C33.2, C34.2, C35.2, C36.2, C37.2, C38.2, C39.2, C40.2, C41.2, C42.2, C43.2, C44.2, C45.2, C48.2, C49.2, C50.2, C51.2, C52.2, C53.2, C54.2, C55.2, C56.2, C57.2, C58.2, C59.2, C60.2, C61.2, C62.2, C63.2, C64.2, C65.2, C66.2, C67.2, C68.2, C69.2, C70.2, C71.2, C72.2, C73.2, C74.2, C75.2, C76.2, C77.2, C78.2, C79.2, C80.2, C81.2, C82.2, C83.2, C84.2, C85.2, C86.2, C87.2, C88.2, C89.2, C90.2, C91.2, C93.2, C94.2, C95.2, C96.2, C97.2, C98.2, C99.2, C100.2, C101.2, C102.2, C103.2, C104.2, C105.2, C106.2, C107.2, C108.2, C109.2, C110.2, C111.2, C112.2, C113.2, C114.2, C115.2, C116.2, C117.2, C118.2, C119.2, C120.2, C121.2, C122.2, C123.2, C124.2, C125.2, C126.2, C127.2, C128.2, C129.2, C130.2, C131.2, C132.2, C133.2, C134.2, C135.2, C136.2, C137.2, C138.2, C139.2, C140.2, C141.2, C142.2, C143.2, CX1.2, J1.1, J1.2, J1.3, J2.7, J2.9, J2.11, J2.13, J2.15, J2.17, J2.19, J2.21, J2.23, J2.25, J2.27, J2.29, J3.1, J3.2, J3.3, J3.4, J3.95, J3.96, J3.97, J3.98, J3.99, J3.100, J4.1, J4.2, J4.3, J4.4, J4.95, J4.96, J4.97, J4.98, J4.99, J4.100, J5.11, J5.13, J5.15, J5.17, J5.18, J5.19, J5.21, J5.23, J5.25, J5.27, J5.29, J6.1, J6.3, J6.5, J6.7, J6.9, J6.11, J6.13, J6.15, J6.17, J6.19, J6.21, J6.23, J6.25, J6.27, J6.29, J6.31, J6.33, J6.35, J7.9, J8.9, J8.10, J8.11, J8.12, J8.39, J8.40, J8.42, J8.45, J8.59, J8.60, J8.61, J8.62, J9.9, J9.10, J9.11, J9.12, J9.39, J9.40, J9.42, J9.45, J9.59, J9.60, J9.61, J9.62, J10.9, J10.10, J10.11, J10.12, J10.39, J10.40, J10.42, J10.45, J10.59, J10.60, J10.61, J10.62, J11.5, JP2.3, JP3.1, JP3.3, JP3.5, JP3.7, JP5.1, JP6.3, JP16.1, JP18.1, JP19.1, R5.2, R7.2, R11.3, R23.2, U1.10, U1.30, U2.10, U2.30, U3.7, U4.7, U5.7, U6.7, U7.7, U8.8, U9.10, U10.7, U11.7, U12.7, U13.7, U14.20, U15.10, U16.1, U16.10, U17.1, U17.10, U17.21, U17.30, U18.2, U18.8, U18.11, U19.7, U20.7, U21.8, U22.4, U22.17, U22.22, U23.7, U24.7, U25.7, U26.4, U26.7, U26.11, U27.7, U28.7, U29.8, U30.7, U31.10, U32.1, U32.6, U32.8, U32.9, U32.14, U33.14, U34.7, U36.8, U37.7, U38.7, U39.8, U40.7, U41.7, U42.8, U43.10, U44.12, U44.21, U45.5, U45.6, U45.8, U46.8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
GRAPH_DG: J3.66, J4.66, U88.4, U89.13, U130.2, U145.13
GREEN: J5.26, U61.13
GraphLD2: J8.35, J9.35, J10.35, U106.8
GraphLD2.2: J3.75, J4.75, U92.11, U106.3
HSYNC: U78.39, UB35.6, UB35.7
HSYNC_EXT: J5.12, RP4.2, UB35.5
High1: RP8.3, U8.6
INT5: JP4.6, JP4.8, U33.23
INT6: JP4.2, JP4.4, U33.24
INT_FDC: R3.1, U14.39, U33.18
INT_KBD_RX: U22.14, U33.22
INT_KBD_TX: JP4.5, U22.15
INT_SER_RX: U33.21, U131.14
INT_SER_TX: JP4.7, U131.15
IORQ: J3.49, J4.49, U8.13, U21.4, U24.11, U39.4
IO_CRTC: U25.10, U39.12, U78.25
IO_FDC: U14.3, U25.9, U39.15
IO_KBD: U22.11, U39.10
IO_LATCH: U13.9, U13.12, U39.14
IO_PIC: U21.13, U33.1
IO_PIO: U39.11, U62.6
IO_REG: U21.11, U106.12
IO_SER: U39.9, U131.11
IO_TIMER: U21.14, U152.21
Index: J2.8, R15.2, U14.35, U47.1
KBD_RxD: J11.2, RP10.8, U22.3
KBD_TxD: J11.1, U22.19
LE_PIXEL: J8.37, J9.37, J10.37, U125.11, U128.12, U146.11
MA0: JP12.8, U79.18, U83.3, U102.3
MA1: JP12.9, U79.16, U83.13
MA2: JP12.14, U79.3, U82.3
MA3: JP12.10, U79.14, U82.13
MA4: JP12.3, U79.5, U81.3
MA5: JP12.7, U79.12, U82.4
MA6: JP12.15, U79.7, U82.12
MA7: JP12.4, U79.9, U81.4
MA8: JP12.11, U81.12, U98.18
MA9: JP12.2, U80.4, U98.3
MA10: JP12.6, U80.12, U98.16
MA11: JP12.16, U98.5, U102.4
MEM?: U41.6, U104.5, U104.10, U135.8, U149.2, U149.5, U149.10, U149.13, U151.1, U151.13
MEMDIS: J3.67, J4.67, RP6.4, U19.9, U44.18
MREQ: U38.3, U71.12
MX0: JP9.3, U83.7
MX1: J8.50, J9.50, J10.50, U83.9, U123.9
MX2: J8.51, J9.51, J10.51, U82.7, U123.3
MX3: J8.52, J9.52, J10.52, U82.9, U123.5
MX4: J8.53, J9.53, J10.53, U81.7, U144.1
MX5: J8.54, J9.54, J10.54, U81.9, U144.5
MX6: J8.55, J9.55, J10.55, U80.7, U144.3
MX7: J8.56, J9.56, J10.56, U80.9, U144.9
MotorOn: J2.16, U51.2
NMI: J3.56, J4.56, RP9.2, U58.15
NVI: J3.52, J4.52, RP9.3, U58.13, U92.6
NVI_ACK: U23.8, U92.1
unnamed: C29.1, R7.1
unnamed: C46.1, U48.6
unnamed: C46.2, R12.1, U48.7
unnamed: C47.1, R13.2, U47.15
unnamed: D2.2, U133.1
unnamed: D3.1, U133.14
unnamed: JP1.1, U114.6, U114.9
unnamed: JP1.2, U112.5
unnamed: JP7.1, U61.11
unnamed: JP19.2, SW1.3
unnamed: R6.2, R8.1
unnamed: R18.2, U61.7, U61.10
unnamed: R20.2, U124.1
unnamed: R9.1, R9.2, R21.2, R22.2
unnamed: R29.2, U152.11, U152.14, U152.16
unnamed: RP3.7, U15.11
unnamed: RP4.6, U33.16
unnamed: RP5.4, U46.3, U46.4, U46.5, U46.6, U46.7
unnamed: RP5.5, U46.1, U46.9, U46.10
unnamed: RP5.6, U45.1, U45.3, U45.4, U45.7, U45.10
unnamed: RP7.2, U48.1
unnamed: RP7.4, U48.2, U48.3
unnamed: RP7.5, U48.10, U48.11
unnamed: RP7.6, U47.10, U47.11
unnamed: RP7.8, U47.9
unnamed: RP8.5, U6.13
unnamed: RP13.6, U77.6
unnamed: RP13.7, U77.8
unnamed: RP14.2, U90.13
unnamed: RP14.8, U92.10
unnamed: RP20.2, U97.3
unnamed: RP20.6, U97.6
unnamed: RP20.7, U97.8
unnamed: RP21.2, U123.2
unnamed: RP21.4, U123.4
unnamed: RP21.6, U123.6
unnamed: RP21.7, U123.8
unnamed: RP24.2, U132.2
unnamed: RP24.3, U132.12
unnamed: RP24.4, U132.5
unnamed: RP24.5, U132.9
unnamed: RP26.7, U144.8
unnamed: U1.1, U1.21
unnamed: U1.2, U1.22
unnamed: U1.11, U1.31
unnamed: U1.12, U1.32
unnamed: U1.13, U1.33
unnamed: U1.14, U1.34
unnamed: U1.15, U1.35
unnamed: U1.16, U1.36
unnamed: U1.17, U1.37
unnamed: U1.18, U1.38
unnamed: U1.19, U1.39
unnamed: U1.3, U1.23
unnamed: U1.4, U1.24
unnamed: U1.5, U1.25
unnamed: U1.6, U1.26
unnamed: U1.7, U1.27
unnamed: U1.8, U1.28
unnamed: U1.9, U1.29
unnamed: U2.1, U2.21
unnamed: U2.2, U2.22
unnamed: U2.11, U2.31
unnamed: U2.12, U2.32
unnamed: U2.13, U2.33
unnamed: U2.14, U2.34
unnamed: U2.15, U2.35
unnamed: U2.16, U2.36
unnamed: U2.17, U2.37
unnamed: U2.18, U2.38
unnamed: U2.19, U2.39
unnamed: U2.3, U2.23
unnamed: U2.4, U2.24
unnamed: U2.5, U2.25
unnamed: U2.6, U2.26
unnamed: U2.7, U2.27
unnamed: U2.8, U2.28
unnamed: U2.9, U2.29
unnamed: U17.2, U17.22
unnamed: U17.11, U17.31
unnamed: U17.12, U17.32
unnamed: U17.13, U17.33
unnamed: U17.14, U17.34
unnamed: U17.15, U17.35
unnamed: U17.16, U17.36
unnamed: U17.17, U17.37
unnamed: U17.18, U17.38
unnamed: U17.19, U17.39
unnamed: U17.3, U17.23
unnamed: U17.4, U17.24
unnamed: U17.5, U17.25
unnamed: U17.6, U17.26
unnamed: U17.7, U17.27
unnamed: U17.8, U17.28
unnamed: U17.9, U17.29
unnamed: U70.3, U70.4
unnamed: U74.1, U74.21
unnamed: U74.2, U74.22
unnamed: U74.11, U74.31
unnamed: U74.12, U74.32
unnamed: U74.13, U74.33
unnamed: U74.14, U74.34
unnamed: U74.15, U74.35
unnamed: U74.16, U74.36
unnamed: U74.17, U74.37
unnamed: U74.18, U74.38
unnamed: U74.19, U74.39
unnamed: U74.3, U74.23
unnamed: U74.4, U74.24
unnamed: U74.5, U74.25
unnamed: U74.6, U74.26
unnamed: U74.7, U74.27
unnamed: U74.8, U74.28
unnamed: U74.9, U74.29
unnamed: U77.5, U77.9, U77.10
unnamed: U107.2, U108.12
unnamed: U111.3, U111.4, U113.5
unnamed: U111.6, U134.4, U134.10
unnamed: U111.5, U111.10, U114.11
unnamed: U84.1, U112.6, U135.3
unnamed: U113.2, U113.6, U134.2
unnamed: U113.3, U113.4
unnamed: U113.10, U113.11
unnamed: U113.8, U113.12, U114.12
unnamed: U114.3, U114.4
unnamed: U114.5, U114.8
unnamed: U90.2, U130.3
unnamed: U134.8, U135.2
unnamed: U134.5, U134.12
unnamed: U135.6, U135.12
N~S: J3.64, J4.64, RP10.4, U69.16
PAR:ACK: J6.20, RP16.10, U110.11
PAR:BUSY: J6.22, RP17.3, U93.17
PAR:DB0: J6.4, RP18.2, U73.18
PAR:DB1: J6.6, RP18.3, U73.17
PAR:DB2: J6.8, RP18.4, U73.16
PAR:DB3: J6.10, RP18.5, U73.15
PAR:DB4: J6.12, RP18.6, U73.14
PAR:DB5: J6.14, RP18.7, U73.13
PAR:DB6: J6.16, RP18.8, U73.12
PAR:DB7: J6.18, RP18.9, U73.11
PAR:DEMAND: J6.30, RP17.4, U93.16
PAR:ERROR: J6.28, RP17.7, U93.13
PAR:PAPER_EMPTY: J6.24, RP17.5, U93.15
PAR:PB0: J6.32, RP17.2, U93.18
PAR:PB6: J6.34, RP17.8
PAR:PB7: J6.36, RP17.9
PAR:PC0: J6.37, RP16.3, U110.18
PAR:PC1: J6.38, RP16.4, U110.16
PAR:PC2: J6.39, JP8.2, RP16.5, U110.15
PAR:PC3: J6.40, RP16.7, U110.14
PAR:PC4: J6.41, JP8.1, RP16.8, U110.7
PAR:PC7_OBF: J6.42, RP16.2, U110.3
PAR:SELECT: J6.26, RP17.6, U93.14
PAR:Strobe: J6.2, RP16.9, U110.12
PB040.2: U129.1, U129.3, U129.6, U129.11, U129.13
PB043: U76.4, U85.9, U94.5, U103.11, U114.1
PC002: U86.8, U126.1, U147.1
PCLK: U72.11, U78.21, U85.3
PC_OR_VT: J3.63, J4.63, JP6.1, RP4.8, U87.13
PG015: JP2.2, U36.4
PIO.PC0: JP4.3, U62.14, U110.2
PIO.PC3: JP4.1, U62.17, U110.6
PIXEL_CLK: J8.38, J9.38, J10.38, U87.8
PL000: U58.1, U59.2, U60.3
PL001: U58.38, U59.3, U60.4
PL002: U58.39, U59.4, U60.7
PL003: U58.40, U59.5, U60.8
PL004: U58.43, U59.6, U60.13
PL005: U58.41, U59.7, U60.14
PL006: U58.44, U59.8, U60.17
PL007: U58.45, U59.9, U60.18
PL008: U58.48, U63.2, U64.3
PL009: U58.2, U63.3, U64.4
PL010: U58.3, U63.4, U64.7
PL011: U58.4, U63.5, U64.8
PL012: U58.5, U63.6, U64.13
PL013: U58.6, U63.7, U64.14
PL014: U58.10, U63.8, U64.17
PL015: U58.9, U63.9, U64.18
PM001: U10.10, U11.5, U28.9
PRGND: J6.43, J7.11
PXL.1: J8.48, U88.5, U89.17
PXL.2: J9.48, U89.11
PXL.3: J10.48, U89.15
PZ017: U90.11, U106.6, U113.9, U124.15, U145.15
PZ020: U75.9, U76.5, U86.2, U94.4, U103.8, U105.1, U105.13, U112.13, U129.5, U135.11
PZ022: U80.14, U81.14, U82.14, U83.14, U85.6, U102.14, U104.11, U150.12
PZ024: JP10.3, U149.3
PZ025: JP10.1, U41.8
PZ030: U18.1, U40.6, U113.1
PZ040: U126.11, U128.2, U147.11
PZ041: U37.9, U104.8
PZ065: U61.2, U72.2, U106.1, U106.5, U106.10, U108.9, U108.10, U124.7, U145.7, UA35.2
RA0: JP12.12, U81.13, U98.14
RA1: JP12.1, U80.3, U98.7
RA2: JP12.5, U80.13, U83.4, U98.12
RA3: JP12.13, U83.12, U98.9
RASU.1: J8.33, J8.34, U129.12
RASU.2: J9.33, J9.34, U129.10
RASU.3: J10.33, J10.34, U129.4
RD: J3.81, J4.81, RP8.8, RP10.7, U3.5, U38.4, U69.7, U70.1, U71.3, U78.22, U86.5, U86.10, U112.11
RED: J5.28, U61.14
RESET: U22.21, U62.35, U91.3, U91.12, U131.21
RING_IND: U93.12, U153.3
ROM-A14: U37.4, U44.9, U80.6
ROM-A15: U37.1, U44.10, U80.10, V.1.1
ROM-TSN0: K.1.3, U37.12, U44.11, U102.6
ROM-TSN1: U44.13, V.1.3, W.1.3
ROM-TSN2: K.1.1, U44.14
RXCLK: JP15.2, U153.8
ReadData: J2.30, R17.1, U48.9
SCLOCK: J3.57, J4.57, U11.2, U28.4, U28.5, U29.13
SDET: U93.11, U153.6
SER_TXC: JP13.1, JP14.1, U131.9
SN0: J3.10, J4.10, U43.2, U44.6
SN1: J3.9, J4.9, U43.5, U44.5
SN2: J3.12, J4.12, U43.6, U44.4
SN3: J3.11, J4.11, U43.9, U44.2
SN4: U26.10, U43.12
SN5: U26.9, U43.15
SN6: U26.8, U43.16
SPARE1: JP3.2, RP3.6, U15.13
ST0: J3.60, J4.60, U8.1, U9.12
ST1: J3.59, J4.59, U8.2, U9.14, U25.2, U44.20
ST2: J3.62, J4.62, U8.3, U9.16, U25.1, U44.3
ST3: J3.61, J4.61, U8.4, U8.5, U9.18, U40.13, U44.19
SYSINT: J3.70, J4.70, RP15.8, U91.5
Select1: J2.10, U51.4
Select2: J2.12, U51.12
SerClk: JP13.3, JP14.2, JP14.3, R27.2, U152.10
SideSelect: J2.32, U30.6
Step: J2.20, U30.12
Track0: J2.26, R16.2, U14.34
V24:CTS: J7.5, U132.10
V24:DSR: J7.4, U132.13
V24:DTR: J7.3, U133.11
V24:RING_IND: J7.8, J7.10, U153.1
V24:RTS: J7.6, U133.8
V24:RX: J7.2, U132.1
V24:RXCLK: J7.13, U153.10
V24:SDET: J7.12, U153.4
V24:TX: J7.1, U133.6
V24:TXCKB: J7.7, U132.4
V24:TXCLKA: J7.16, U133.3
VDMX-CRTC: U80.2, U81.2, U82.2, U83.2, U102.2, U112.8
VI: J3.58, J4.58, RP9.4, U50.10, U58.12
VINTACK: J3.68, J4.68, U3.11, U4.3, U33.26
VI_ACK: RP1.2, U3.13, U20.12
VSYNC: U78.40, UB35.1, UB35.2
VSYNC_EXT: J5.20, RP4.3, UB35.3
VT_CS: J3.88, J4.88, U75.6
VT_LATCH: J3.85, J4.85, U94.6
VT_WE: J3.87, J4.87, U75.8
VTbl: J3.79, J4.79, U61.5, U88.7, U89.3
VTgr: J3.80, J4.80, U61.4, U88.9, U89.7
VTin: U61.6, U88.6, U89.5
VTrd: J3.77, J4.77, U61.3, U88.10, U89.9
WE.H: J8.58, J9.58, J10.58, U77.1, U151.6
WE.L: J8.57, J9.57, J10.57, U77.11, U151.8
WriteData: J2.22, U30.8
WriteGate: J2.24, U30.2
WriteProtect: J2.28, R14.2, U14.36
X.107.6: U106.2, U106.4, U106.9, U107.6
X.108.4: U108.4, U134.3, U134.11
XA.5.9: U5.9, U10.9, U11.1
XA.10.8: U10.8, U23.12
XA.23.6: U23.6, U40.3
XA.95.1: U86.4, U86.11, U95.1
out_buf_en: J3.45, J4.45, U86.6
wr_buf_en: J3.46, J4.46, U86.12
~AS: J3.55, J4.55, RP10.2, U5.2, U6.11, U69.18, U71.11
~BOOT: J3.51, J4.51, RP2.7, U20.8
~BUSACKIN: J3.48, J4.48, RP12.7, U70.9
~BUSACKOUT: J3.47, J4.47, RP12.5, U70.5, U71.8
~CPU_OP: U9.1, U43.1, U60.1, U64.1, U69.1, U69.19, U70.8, U71.9
~DRAM: RP6.7, U25.13, U42.5, U44.15, U128.3
~DS: J3.53, J4.53, RP10.5, U3.10, U24.12, U69.5, U70.2, U71.1, U95.2
~MREQ: J3.84, J4.84, JP2.1, RP10.6, U24.6, U69.14, U71.13
~RD: U3.1, U59.1, U63.1, U71.4, U86.1, U105.2, U105.12
~RDIO: U3.6, U13.10, U14.4, U22.13, U33.3, U62.5, U131.13, U152.22
~RESET: J11.4, U5.4, U5.13, U6.10, U14.19, U18.10, U23.10, U37.10, U52.1, U78.2, U90.1, U91.4, U92.13, U111.1, U124.9, U145.9
~ROM: RP6.5, U38.11, U44.17
~SCLK: JP.AA.1.1, U5.3, U5.11, U19.1, UA28.3
~SRAM: J3.83, J4.83, RP6.6, U25.12, U44.16, U87.1, U87.2, U95.5
~SRESET: J3.50, J4.50, RP14.4, U50.8, U91.13
~SWAIT: J3.54, J4.54, RP2.8, U20.6, U27.1
~WAIT: J3.78, J4.78, RP6.2, U27.3
~WRIO: U3.3, U13.13, U14.2, U22.10, U33.2, U62.36, U106.13, U131.10, U152.23

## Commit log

2023-02-08 add pcb layout
2023-02-08 convert to kicad6
2023-02-08 convert pcb to kicad6
2023-02-11 fixing KiCad6 warnings
